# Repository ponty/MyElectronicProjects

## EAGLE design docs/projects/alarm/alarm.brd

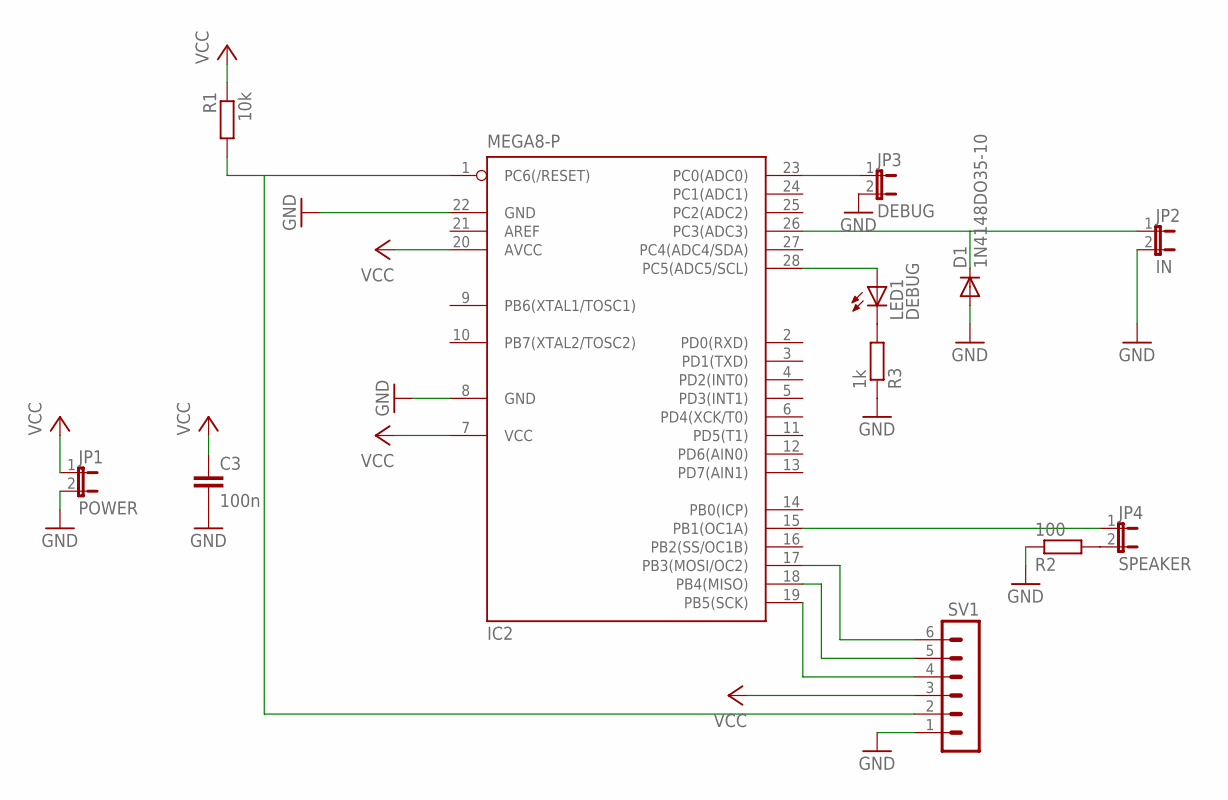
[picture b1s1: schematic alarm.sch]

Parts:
C3: 100n; C025-024X044
D1: 1N4148DO35-10; DO35-10
IC2: MEGA8-P; DIL28-3
JP1: POWER; JP1
JP2: IN; JP1
JP3: DEBUG; JP1
JP4: SPEAKER; JP1
LED1: DEBUG; LED5MM
R1: 10k; 0207/15
R2: 100; M0805
R3: 1k; 0617/17
SV1: MA06-1

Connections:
GND: C3.2, D1.A, IC2.8 (GND), IC2.22 (GND), JP1.2, JP2.2, JP3.2, R2.1, R3.1, SV1.1
unnamed: JP4.2, R2.2
unnamed: D1.C, IC2.26 (PC3(ADC3)), JP2.1
unnamed: IC2.15 (PB1(OC1A)), JP4.1
unnamed: IC2.23 (PC0(ADC0)), JP3.1
unnamed: IC2.19 (PB5(SCK)), SV1.4
unnamed: IC2.18 (PB4(MISO)), SV1.5
unnamed: IC2.17 (PB3(MOSI/OC2)), SV1.6
unnamed: LED1.K (C), R3.2
unnamed: IC2.28 (PC5(ADC5/SCL)), LED1.A
unnamed: IC2.1 (PC6(/RESET)), R1.2, SV1.2
VCC: C3.1, IC2.7 (VCC), IC2.20 (AVCC), JP1.1, R1.1, SV1.3

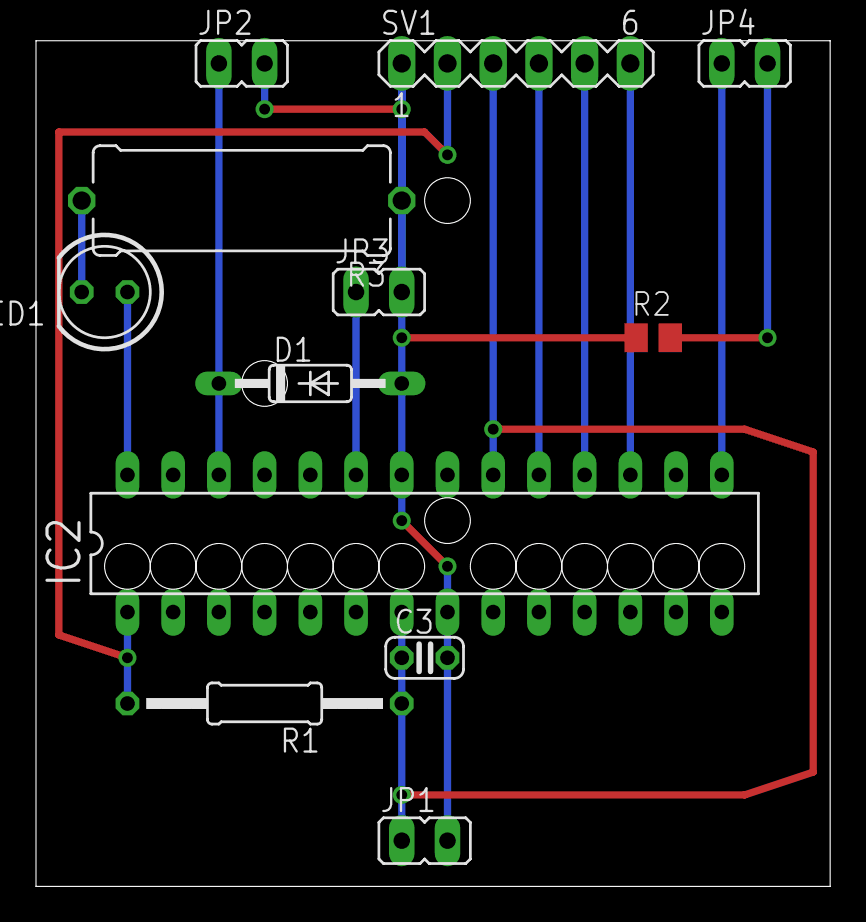
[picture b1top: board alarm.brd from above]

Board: 2 copper layers, 44.1 x 47.0 mm, 12 parts (0 on the bottom side), 12 nets.

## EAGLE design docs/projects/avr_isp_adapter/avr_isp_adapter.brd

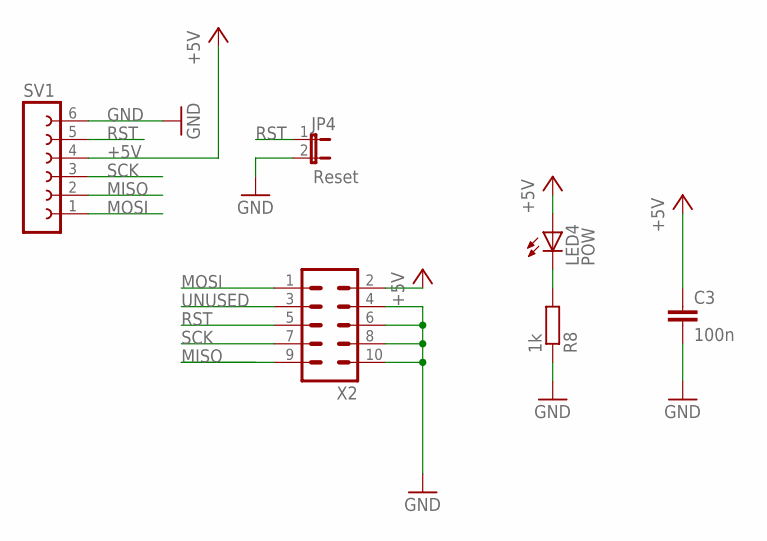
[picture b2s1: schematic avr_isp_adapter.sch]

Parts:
C3: 100n; C050-025X075
JP4: Reset; JP1
LED4: POW; LED5MM
R8: 1k; 0204/5
SV1: FE06W
X2: ML10L

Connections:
+5V: C3.1, LED4.A, SV1.4, X2.2
GND: C3.2, JP4.2, R8.1, SV1.6, X2.4, X2.6, X2.8, X2.10
MISO: SV1.2, X2.9
MOSI: SV1.1, X2.1
unnamed: LED4.K (C), R8.2
RST: JP4.1, SV1.5, X2.5
SCK: SV1.3, X2.7
UNUSED: X2.3

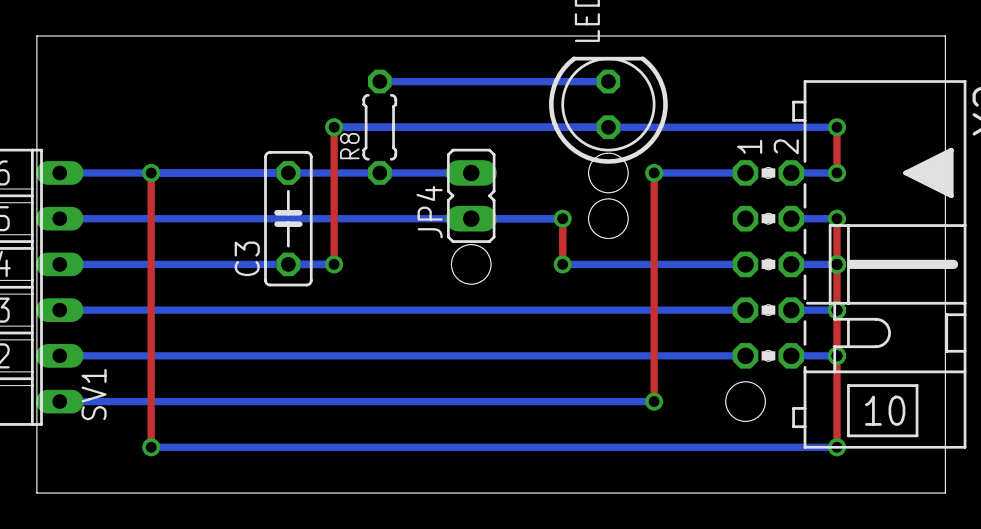
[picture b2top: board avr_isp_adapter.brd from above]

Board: 2 copper layers, 50.5 x 25.4 mm, 6 parts (0 on the bottom side), 7 nets.

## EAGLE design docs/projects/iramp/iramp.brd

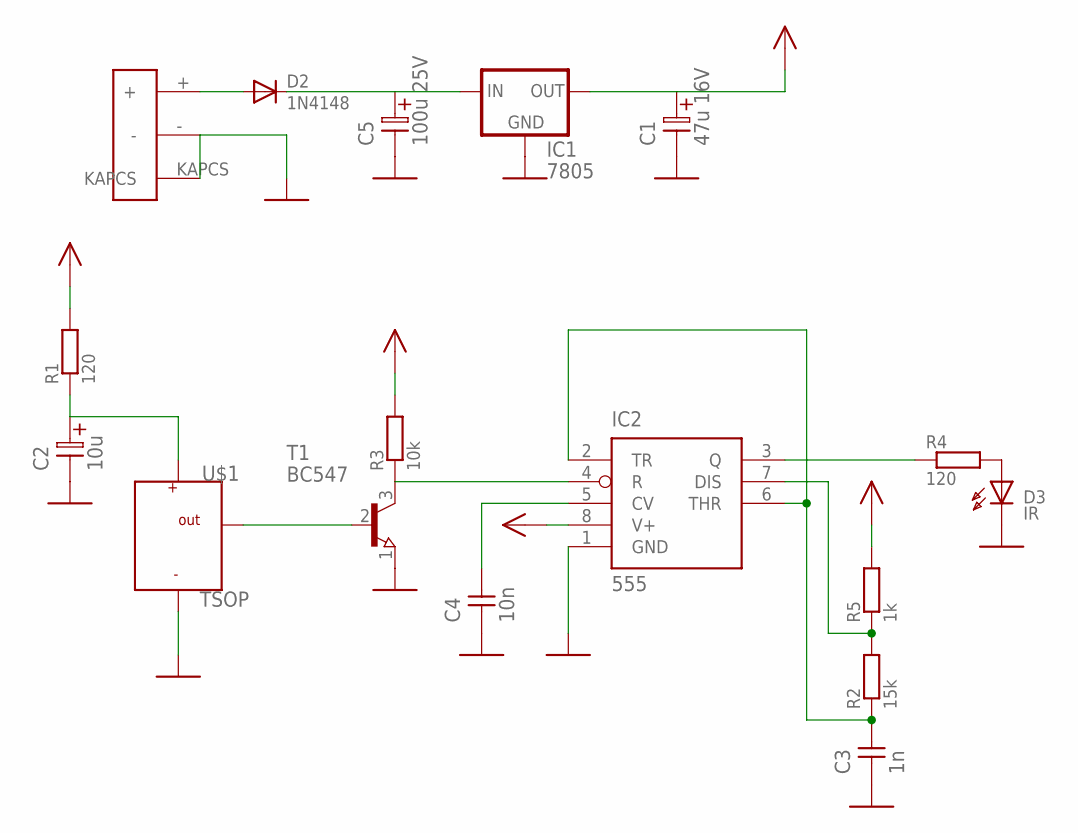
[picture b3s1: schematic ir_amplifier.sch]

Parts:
C1: 47u 16V; ES-2,5L
C2: 10u; ES-2,5L
C3: 1n; C-5
C4: 10n; C-5
C5: 100u 25V; ES-5
D2: 1N4148; DO35-10
D3: IR; LED5
IC1: 7805; 78XXS
IC2: 555; DIL8
R1, R4: 120; 0207/10
R2: 15k; 0207/10
R3: 10k; 0207/10
R5: 1k; 0207/10
T1: BC547; TO92
U$1: TSOP
U$2: DC ALJ; DC_ALJ

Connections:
GND: C1.2, C2.2, C3.1, C4.1, C5.2, D3.K, IC1.GND, IC2.1 (GND), T1.1 (E), U$1.-, U$2.-, U$2.KAPCS
unnamed: C3.2, IC2.2 (TR), IC2.6 (THR), R2.1
unnamed: IC2.3 (Q), R4.1
unnamed: C2.1, R1.1, U$1.+
unnamed: D3.A, R4.2
unnamed: D2.A, U$2.+
unnamed: C5.1, D2.K, IC1.IN
unnamed: T1.2 (B), U$1.OUT
unnamed: IC2.4 (R), R3.1, T1.3 (C)
unnamed: C4.2, IC2.5 (CV)
unnamed: IC2.7 (DIS), R2.2, R5.1
VCC: C1.1, IC1.OUT, IC2.8 (V+), R1.2, R3.2, R5.2

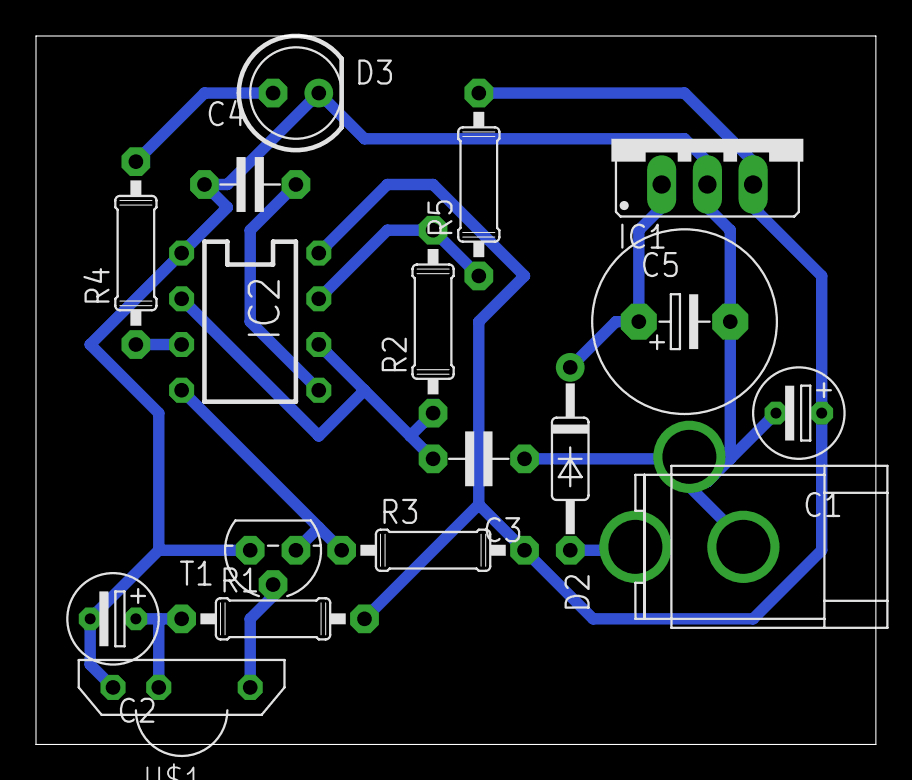
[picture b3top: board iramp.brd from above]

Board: 1 copper layer, 46.7 x 39.4 mm, 17 parts (0 on the bottom side), 12 nets.

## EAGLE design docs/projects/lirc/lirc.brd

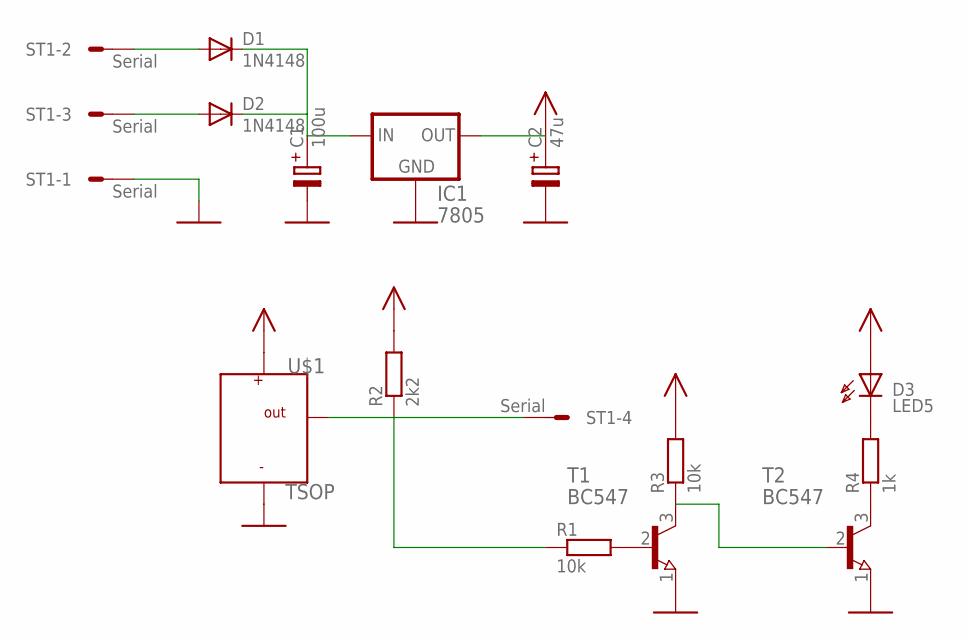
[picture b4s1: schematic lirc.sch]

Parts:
C1: 100u; E30-10
C2: 47u; E25-10
D1, D2: 1N4148; DO35-10
D3: LED5
IC1: 7805; 78XXS
R1, R3: 10k; 0207/10
R2: 2k2; 0207/10
R4: 1k; 0207/10
ST1: Serial; MSF4
T1, T2: BC547; TO92
U$1: TSOP

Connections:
GND: C1.-, C2.-, IC1.GND, ST1.1, T1.1 (E), T2.1 (E), U$1.-
unnamed: C1.+, D1.K, D2.K, IC1.IN
unnamed: R4.1, T2.3 (C)
unnamed: R3.1, T1.3 (C), T2.2 (B)
unnamed: R1.2, T1.2 (B)
unnamed: D3.K, R4.2
unnamed: D1.A, ST1.2
unnamed: D2.A, ST1.3
unnamed: R1.1, R2.1, ST1.4, U$1.OUT
VCC: C2.+, D3.A, IC1.OUT, R2.2, R3.2, U$1.+

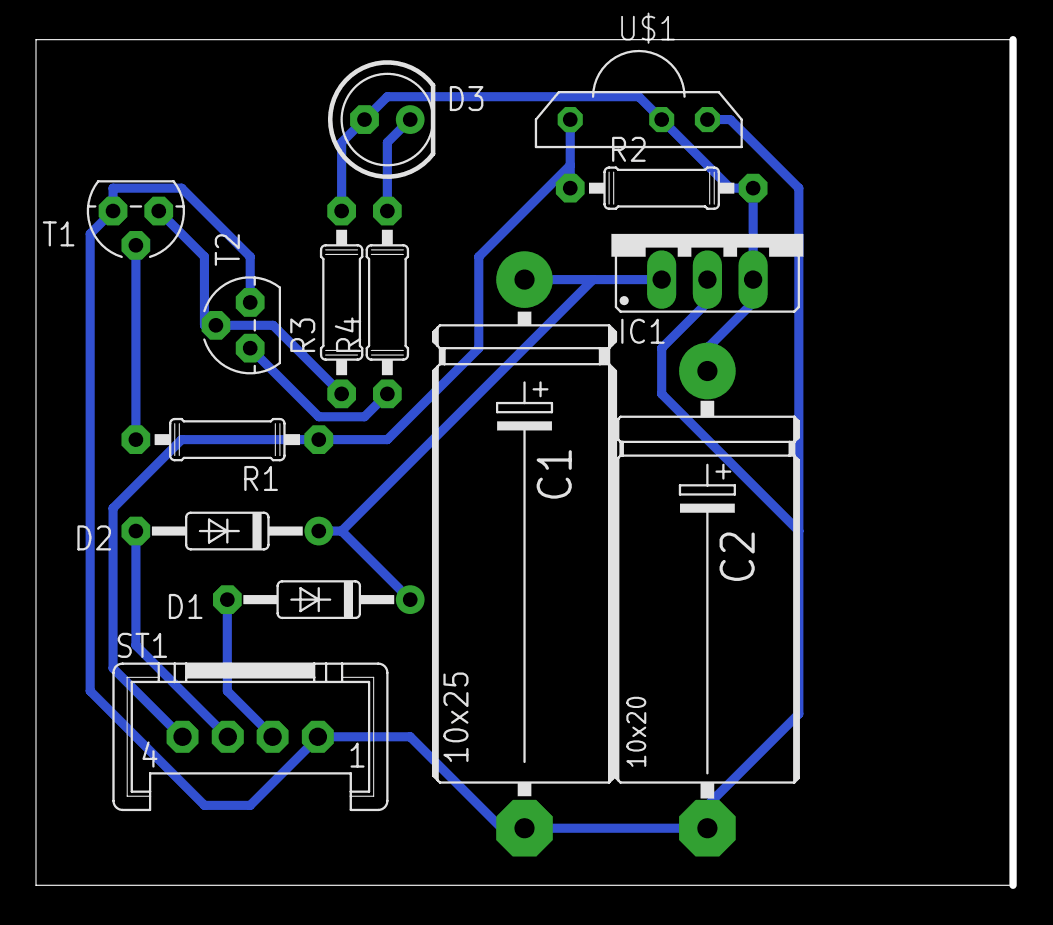
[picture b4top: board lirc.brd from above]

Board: 1 copper layer, 54.3 x 47.0 mm, 14 parts (0 on the bottom side), 10 nets.
